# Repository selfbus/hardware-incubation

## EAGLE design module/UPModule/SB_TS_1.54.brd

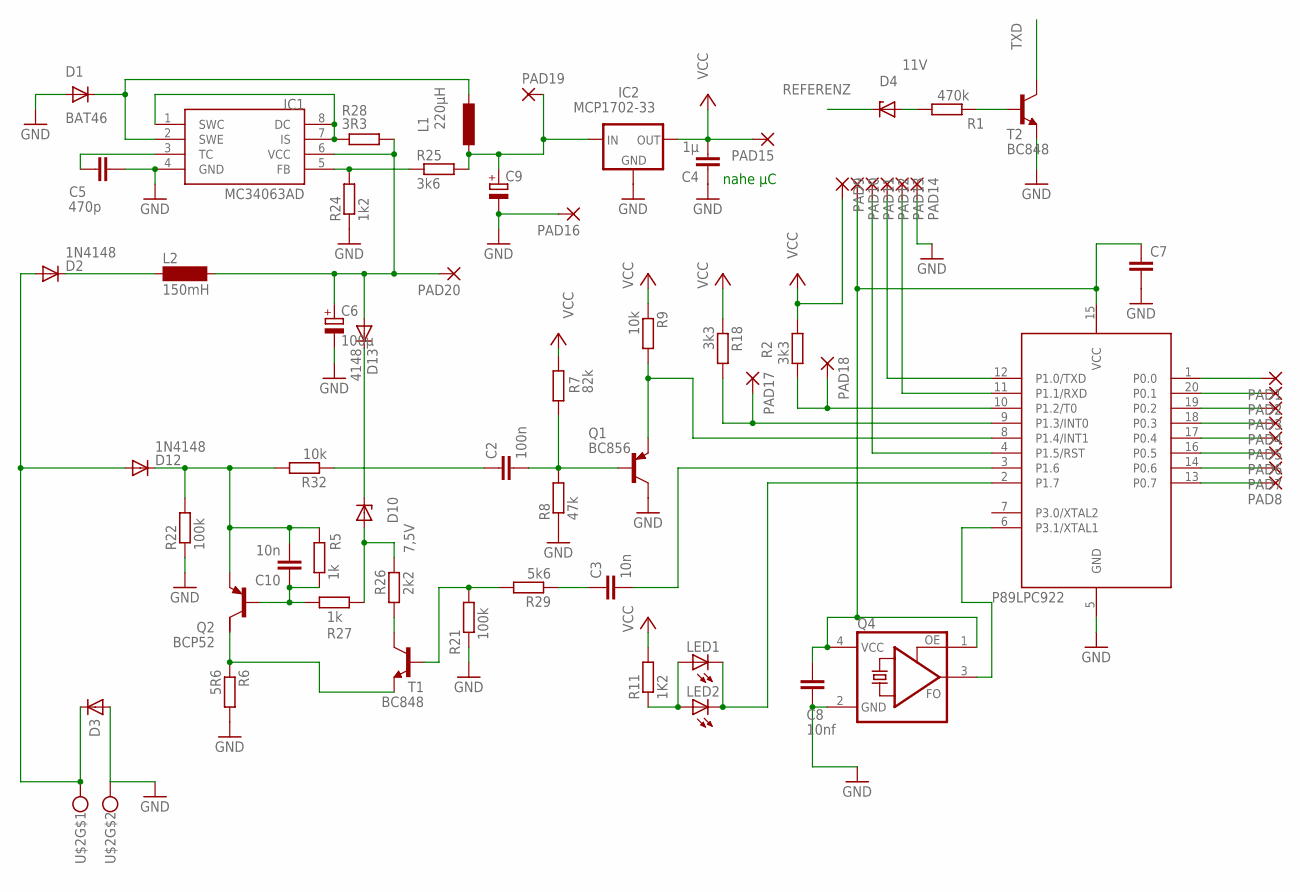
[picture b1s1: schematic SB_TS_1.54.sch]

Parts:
C2: 100n; C1206
C3, C10: 10n; C1206
C4: 1µ; C1206
C5: 470p; C1206
C6: 100µ; SANYO-OSCON_SMD_C6
C7: C-EUC1206; C1206
C8: 10nf; C1206
C9: CPOL-EUE2.5-5; E2,5-5
D1: BAT46; MINIMELF
D2, D12: 1N4148; MINIMELF
D3: SMAJ40AC; SMB
D4: 11V; MINIMELF
D10: 7,5V; MINIMELF
D13: 4148; MINIMELF
IC1: MC34063AD; SOIC8
IC2: MCP1702-33; 79LXX
L1: 220µH; 2200-11.43
L2: 150mH; SD12_1000
LED1: LEDCHIPLED_1206; CHIPLED_1206
LED2: LED3MM
PAD1, PAD2, PAD3, PAD4, PAD5, PAD6, PAD7, PAD8, PAD9, PAD10, PAD11, PAD12, PAD13, PAD14, PAD15, PAD16, PAD17, PAD18, PAD19, PAD20: SMD2; SMD1,27-2,54
Q1: BC856; SOT23-BEC
Q2: BCP52; SOT223
Q4: ASFL; ASF
R1: 470k; R1206
R2: 3k3; M1206
R5, R27: 1k; R1206
R6: 5R6; R1206
R7: 82k; R1206
R8: 47k; M1206
R9, R32: 10k; R1206
R11: 1K2; R1206
R18: 3k3; R1206
R21: 100k; R1206
R22: 100k; M1206
R24: 1k2; R1206
R25: 3k6; M1206
R26: 2k2; M1206
R28: 3R3; M1206
R29: 5k6; R1206
T1, T2: BC848; SOT23
U1: 89LPC922; DIL20
U$2: AKL059-02; AKL3.5X2

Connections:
A_PUNKT_EIBIN: C2.2, Q1.B, R7.1, R8.2
BASE_SEND: R21.2, R29.2, T1.1 (B)
BASE_SEND_AMP: C10.1, Q2.1 (B), R5.1, R27.2
CURR_SENSE: Q2.2 (C), R6.1, T1.2 (E)
C_T1: R26.1, T1.3 (C)
EIB+: D2.A, D3.1 (C), D12.A, U$2.1
EIBIN: Q1.E, R9.2, U1.8 (P1.4/INT1)
EIB_DC1: C6.+, D13.A, IC1.6 (VCC), L2.2, PAD20.1, R28.2
EIB_SEND: C3.2, U1.3 (P1.6)
GND: C4.1, C5.2, C6.-, C7.2, C8.2, C9.-, D1.A, D3.2 (A), IC1.4 (GND), IC2.GND, PAD14.1, PAD16.1, Q1.C, Q4.2 (GND), R6.2, R8.1, R21.1, R22.1, R24.1, T2.2 (E), U1.5 (GND), U$2.2
INT0: PAD17.1, R18.2, U1.9 (P1.3/INT0)
unnamed: D4.A, R1.2
unnamed: C3.1, R29.1
unnamed: R1.1, T2.1 (B)
unnamed: C10.2, D12.C, Q2.3 (E), R5.2, R22.2, R32.2
unnamed: D2.C, L2.1
unnamed: LED1.A, LED2.A, R11.1
unnamed: D1.C, IC1.2 (SWE), L1.2
unnamed: C5.1, IC1.3 (TC)
unnamed: D10.C, D13.C
unnamed: IC1.1 (SWC), IC1.7 (IS), IC1.8 (DC), R28.1
unnamed: C2.1, R32.1
OSCCLK: Q4.3 (FO), U1.6 (P3.1/XTAL1)
P00: PAD1.1, U1.1 (P0.0)
P01: PAD2.1, U1.20 (P0.1)
P02: PAD3.1, U1.19 (P0.2)
P03: PAD4.1, U1.18 (P0.3)
P04: PAD5.1, U1.17 (P0.4)
P05: PAD6.1, U1.16 (P0.5)
P06: PAD7.1, U1.14 (P0.6)
P07: PAD8.1, U1.13 (P0.7)
PROG: LED1.C, LED2.K (C), U1.2 (P1.7)
PWM: PAD18.1, R2.2, U1.10 (P1.2/T0)
REFERENZ: D4.C, D10.A, R26.2, R27.1
RESET: PAD11.1, U1.4 (P1.5/RST)
RXD: PAD13.1, U1.11 (P1.1/RXD)
TXD: PAD12.1, T2.3 (C), U1.12 (P1.0/TXD)
VCC: C4.2, IC2.OUT, PAD9.1, PAD15.1, R2.1, R7.2, R9.1, R11.2, R18.1
VCC5V: C9.+, IC2.IN, L1.1, PAD19.1, R25.2
VCC_FEEDBACK: IC1.5 (FB), R24.2, R25.1
VCC_LPC: C7.1, C8.1, PAD10.1, Q4.1 (OE), Q4.4 (VCC), U1.15 (VCC)

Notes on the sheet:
nahe µC
P89LPC922

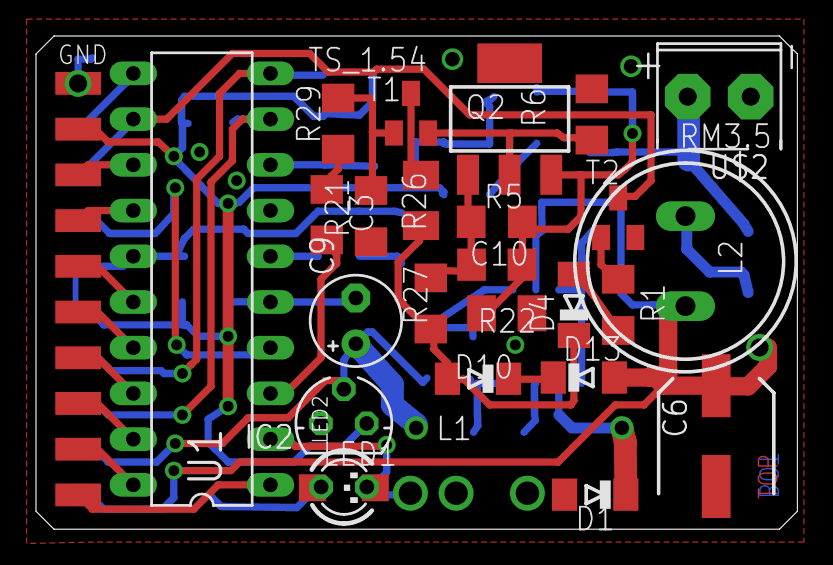
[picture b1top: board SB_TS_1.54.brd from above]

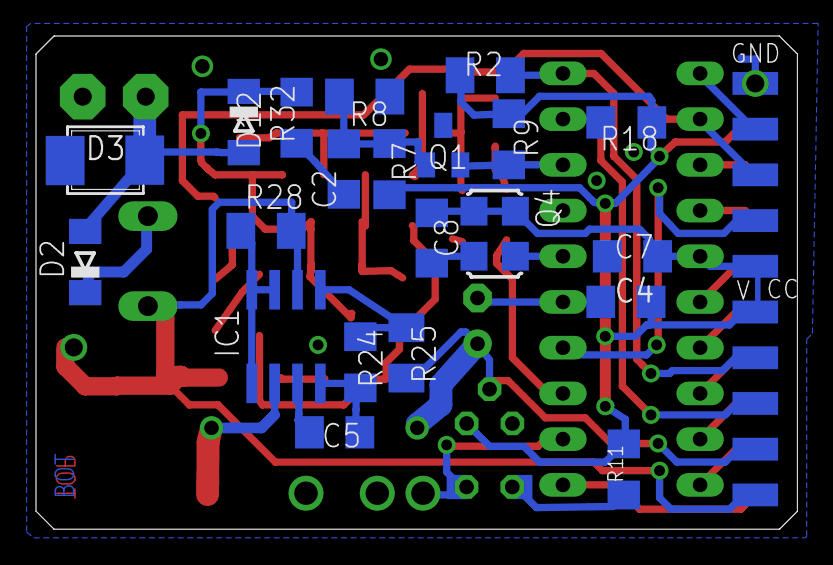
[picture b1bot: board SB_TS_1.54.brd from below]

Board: 2 copper layers, 42.3 x 27.4 mm, 67 parts (31 on the bottom side), 41 nets.

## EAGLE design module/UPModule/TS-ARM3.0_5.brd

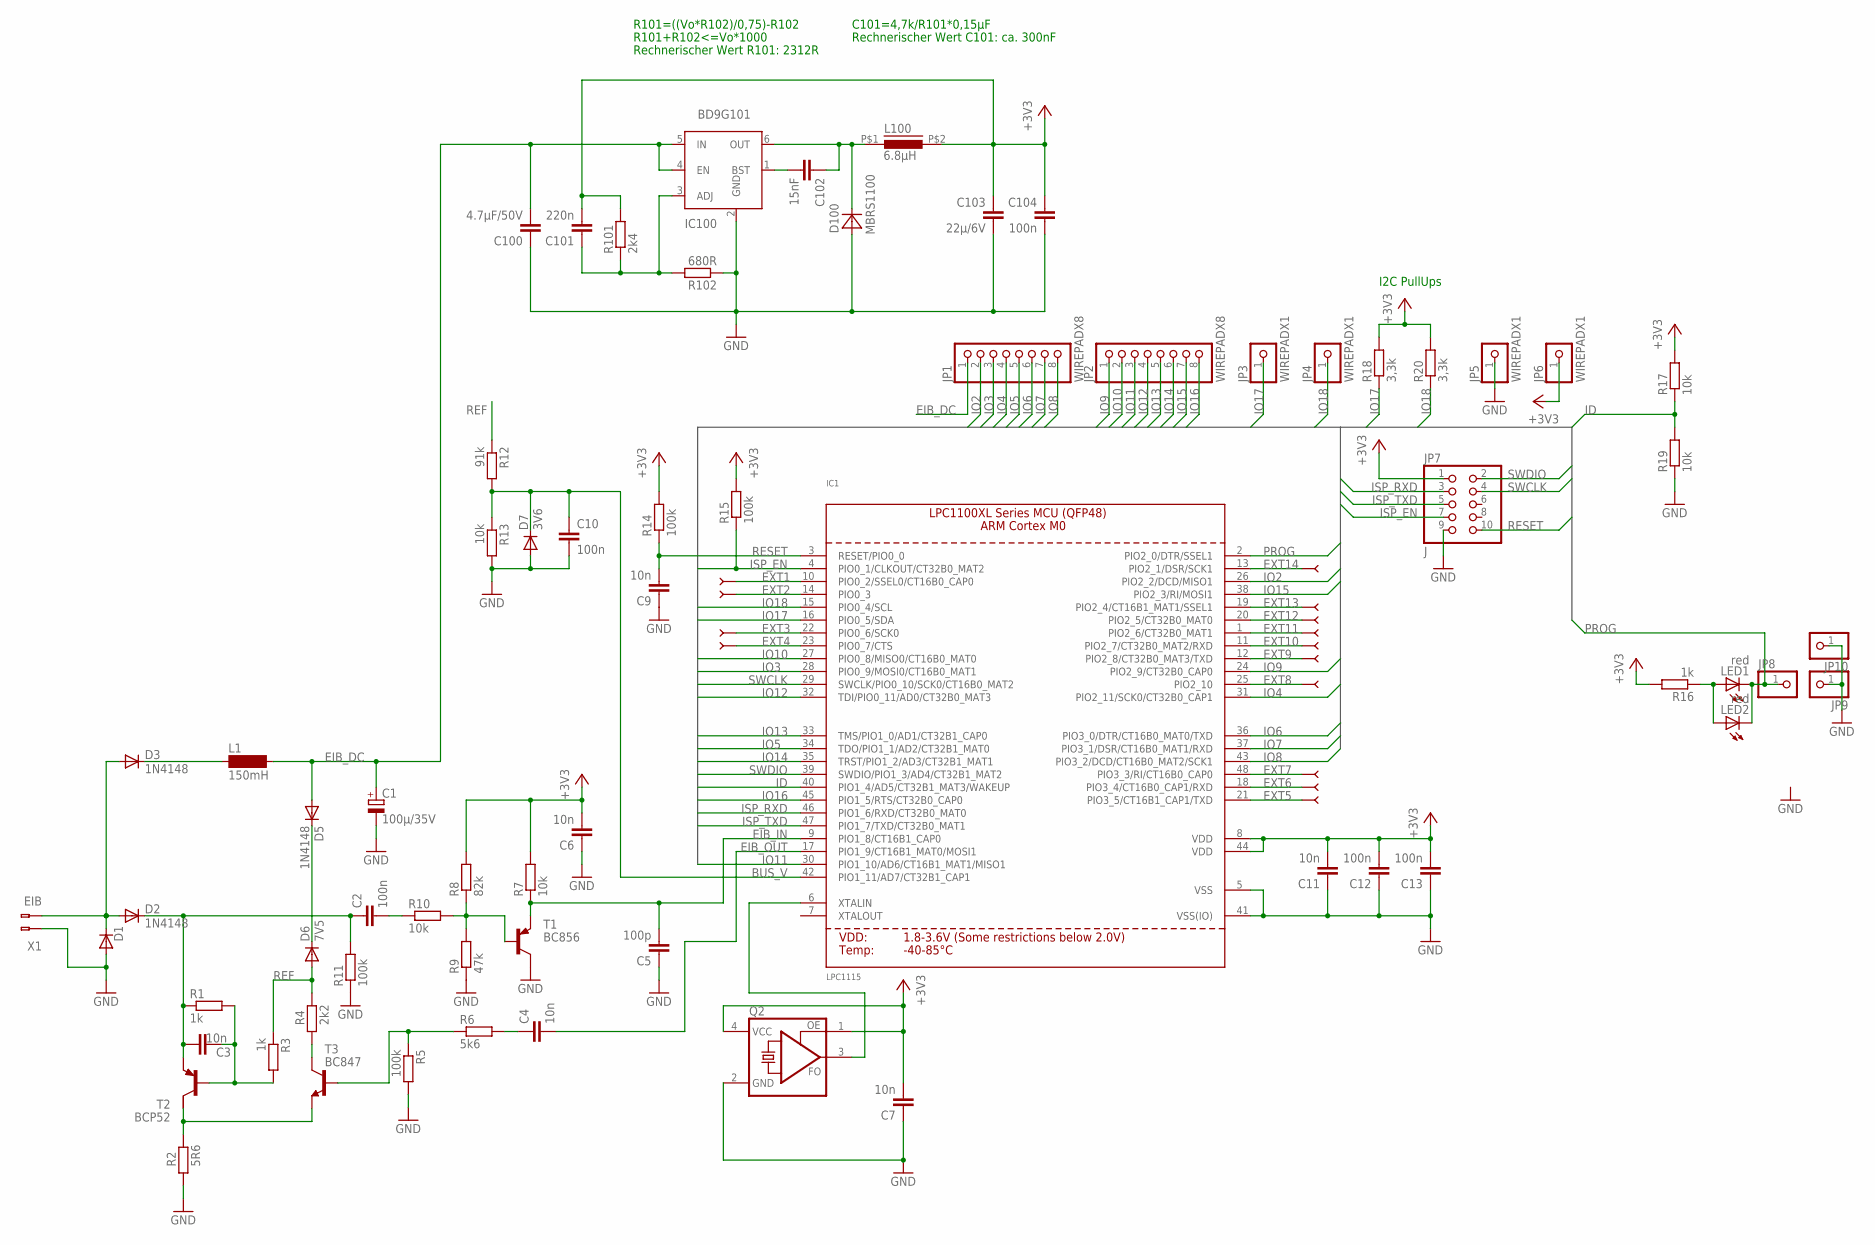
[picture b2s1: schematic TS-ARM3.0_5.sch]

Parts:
C1: 100µ/35V; SANYO-OSCON_SMD_C6
C2, C10, C12, C13, C104: 100n; C1206
C3, C4, C6, C7, C9, C11: 10n; C1206
C5: 100p; C1206
C100: 4.7µF/50V; C1206
C101: 220n; C1206
C102: 15nF; C1206
C103: 22µ/6V; C1206
D1: SMAJ40C; SMB
D2, D3, D5: 1N4148; MINIMELF
D6: 7V5; MINIMELF
D7: 3V6; MINIMELF
D100: MBRS1100; SMA
IC1: LPC1115; LQFP48
IC100: BD9G101; SOT23-6
JP1, JP2: WIREPADX8; SMD1,27X2,54X8
JP3, JP4, JP5, JP6: WIREPADX1; SMD1,27X2,54
JP7: J; 2X05M
JP8, JP9, JP10: PINHD-1X1; 1X01
L1: 150mH; SD12_1000
L100: 6.8µH; PIS2812
LED1: red; CHIPLED_1206
LED2: red; LED3MM
P1, P2, P3, P4, P5, P6, P7, P8, P9, P10, P11, P12, P13, P14: PAD
Q2: ASFL; ASF
R1, R3, R16: 1k; R1206
R2: 5R6; R1206
R4: 2k2; R1206
R5, R11, R14, R15: 100k; R1206
R6: 5k6; R1206
R7, R10, R13, R17, R19: 10k; R1206
R8: 82k; R1206
R9: 47k; R1206
R12: 91k; R1206
R18, R20: 3,3k; R1206
R101: 2k4; R1206
R102: 680R; R1206
T1: BC856; SOT23-BEC
T2: BCP52; SOT223
T3: BC847; SOT23
X1: EIB; BUSKLEMME243-724

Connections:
+3V3: C6.2, C7.2, C11.2, C12.2, C13.2, C101.2, C103.1, C104.1, IC1.8 (VDD), IC1.44 (VDD), JP6.1, JP7.1, L100.P$2 (2), Q2.1 (OE), Q2.4 (VCC), R7.2, R8.2, R14.2, R15.2, R16.2, R17.2, R18.2, R20.2, R101.2
BUS_V: C10.2, D7.C, IC1.42 (PIO1_11/AD7/CT32B1_CAP1), R12.2, R13.1
DRAIN: C2.1, C3.1, D2.C, R1.1, R11.2, T2.3 (E)
EIB+: D1.1 (C), D2.A, D3.A, X1.2 (B-2)
EIB_DC: C1.+, C100.2, D5.A, IC100.4 (EN), IC100.5 (IN), JP1.1, L1.2
EIB_IN: C5.2, IC1.9 (PIO1_8/CT16B1_CAP0), R7.1, T1.E
EIB_OUT: C4.2, IC1.17 (PIO1_9/CT16B1_MAT0/MOSI1)
EXT1: IC1.10 (PIO0_2/SSEL0/CT16B0_CAP0), P1.1
EXT2: IC1.14 (PIO0_3), P2.1
EXT3: IC1.22 (PIO0_6/SCK0), P13.1
EXT4: IC1.23 (PIO0_7/CTS), P14.1
EXT5: IC1.21 (PIO3_5/CT16B1_CAP1/TXD), P12.1
EXT6: IC1.18 (PIO3_4/CT16B0_CAP1/RXD), P11.1
EXT7: IC1.48 (PIO3_3/RI/CT16B0_CAP0), P10.1
EXT8: IC1.25 (PIO2_10), P6.1
EXT9: IC1.12 (PIO2_8/CT32B0_MAT3/TXD), P4.1
EXT10: IC1.11 (PIO2_7/CT32B0_MAT2/RXD), P5.1
EXT11: IC1.1 (PIO2_6/CT32B0_MAT1), P9.1
EXT12: IC1.20 (PIO2_5/CT32B0_MAT0), P8.1
EXT13: IC1.19 (PIO2_4/CT16B1_MAT1/SSEL1), P7.1
EXT14: IC1.13 (PIO2_1/DSR/SCK1), P3.1
GND: C1.-, C5.1, C6.1, C7.1, C9.1, C10.1, C11.1, C12.1, C13.1, C100.1, C103.2, C104.2, D1.2 (A), D7.A, D100.A, IC1.5 (VSS), IC1.41 (VSS(IO)), IC100.2 (GND), JP5.1, JP7.9, JP9.1, JP10.1, Q2.2 (GND), R2.1, R5.2, R9.1, R11.1, R13.2, R19.1, R102.1, T1.C, X1.1 (B-1)
ID: IC1.40 (PIO1_4/AD5/CT32B1_MAT3/WAKEUP), R17.1, R19.2
IO2: IC1.26 (PIO2_2/DCD/MISO1), JP1.2
IO3: IC1.28 (PIO0_9/MOSI0/CT16B0_MAT1), JP1.3
IO4: IC1.31 (PIO2_11/SCK0/CT32B0_CAP1), JP1.4
IO5: IC1.34 (TDO/PIO1_1/AD2/CT32B1_MAT0), JP1.5
IO6: IC1.36 (PIO3_0/DTR/CT16B0_MAT0/TXD), JP1.6
IO7: IC1.37 (PIO3_1/DSR/CT16B0_MAT1/RXD), JP1.7
IO8: IC1.43 (PIO3_2/DCD/CT16B0_MAT2/SCK1), JP1.8
IO9: IC1.24 (PIO2_9/CT32B0_CAP0), JP2.1
IO10: IC1.27 (PIO0_8/MISO0/CT16B0_MAT0), JP2.2
IO11: IC1.30 (PIO1_10/AD6/CT16B1_MAT1/MISO1), JP2.3
IO12: IC1.32 (TDI/PIO0_11/AD0/CT32B0_MAT3), JP2.4
IO13: IC1.33 (TMS/PIO1_0/AD1/CT32B1_CAP0), JP2.5
IO14: IC1.35 (TRST/PIO1_2/AD3/CT32B1_MAT1), JP2.6
IO15: IC1.38 (PIO2_3/RI/MOSI1), JP2.7
IO16: IC1.45 (PIO1_5/RTS/CT32B0_CAP0), JP2.8
IO17: IC1.16 (PIO0_5/SDA), JP3.1, R18.1
IO18: IC1.15 (PIO0_4/SCL), JP4.1, R20.1
ISP_EN: IC1.4 (PIO0_1/CLKOUT/CT32B0_MAT2), JP7.7, R15.1
ISP_RXD: IC1.46 (PIO1_6/RXD/CT32B0_MAT0), JP7.3
ISP_TXD: IC1.47 (PIO1_7/TXD/CT32B0_MAT1), JP7.5
LX: C102.1, D100.C, IC100.6 (OUT), L100.P$1 (1)
unnamed: C2.2, R10.1
unnamed: C101.1, IC100.3 (ADJ), R101.1, R102.2
unnamed: C4.1, R6.2
unnamed: IC1.6 (XTALIN), Q2.3 (FO)
unnamed: R4.1, T3.3 (C)
unnamed: R2.2, T2.2 (C), T3.2 (E)
unnamed: D3.C, L1.1
unnamed: D5.C, D6.C
unnamed: R5.1, R6.1, T3.1 (B)
unnamed: R8.1, R9.2, R10.2, T1.B
unnamed: C3.2, R1.2, R3.2, T2.1 (B)
unnamed: C102.2, IC100.1 (BST)
unnamed: LED1.A, LED2.A, R16.1
PROG: IC1.2 (PIO2_0/DTR/SSEL1), JP8.1, LED1.C, LED2.K (C)
REF: D6.A, R3.1, R4.2, R12.1
RESET: C9.2, IC1.3 (RESET/PIO0_0), JP7.10, R14.1
SWCLK: IC1.29 (SWCLK/PIO0_10/SCK0/CT16B0_MAT2), JP7.4
SWDIO: IC1.39 (SWDIO/PIO1_3/AD4/CT32B1_MAT2), JP7.2

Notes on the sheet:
R101=((Vo*R102)/0,75)-R102
R101+R102<=Vo*1000
Rechnerischer Wert R101: 2312R
C101=4,7k/R101*0,15µF
Rechnerischer Wert C101: ca. 300nF
I2C PullUps

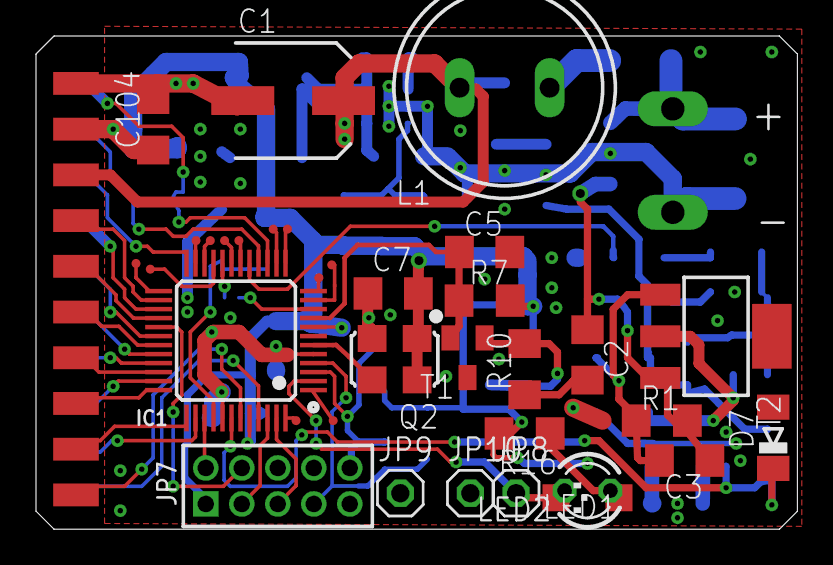
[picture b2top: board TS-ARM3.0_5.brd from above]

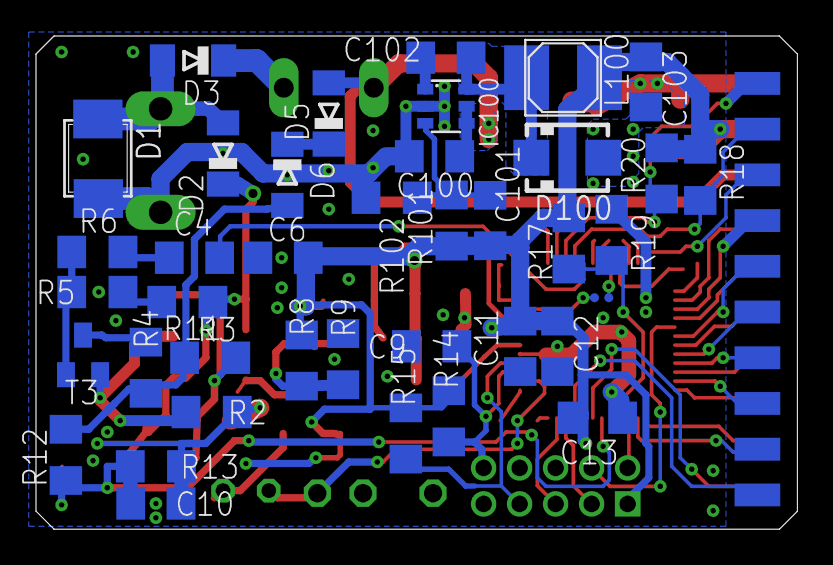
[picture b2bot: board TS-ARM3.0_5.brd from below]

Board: 2 copper layers, 42.3 x 27.4 mm, 81 parts (43 on the bottom side), 62 nets.

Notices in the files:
parts and their libraries:
microbuilder: This work is placed in the public domain, and may be freely used for commercial and non-commercial work with the following conditions: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
